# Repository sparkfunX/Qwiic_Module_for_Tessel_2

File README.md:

Qwiic Module for Tessel 2
========================================

[*SPX-14334*](https://www.sparkfun.com/products/14334)

A small breakout board to connect the Tessel 2 to the Qwiic System.

The [Qwiic system](http://www.sparkfun.com/qwiic) enables fast and solderless connection between popular platforms and various sensors and actuators. You can read more about the Qwiic system [here](http://www.sparkfun.com/qwiic). 

License Information
-------------------

This product is _**open source**_!

Please review the LICENSE.md file for license information.

If you have any questions or concerns on licensing, please contact techsupport@sparkfun.com.

Distributed as-is; no warranty is given.

- Your friends at SparkFun.

_<COLLABORATION CREDIT>_

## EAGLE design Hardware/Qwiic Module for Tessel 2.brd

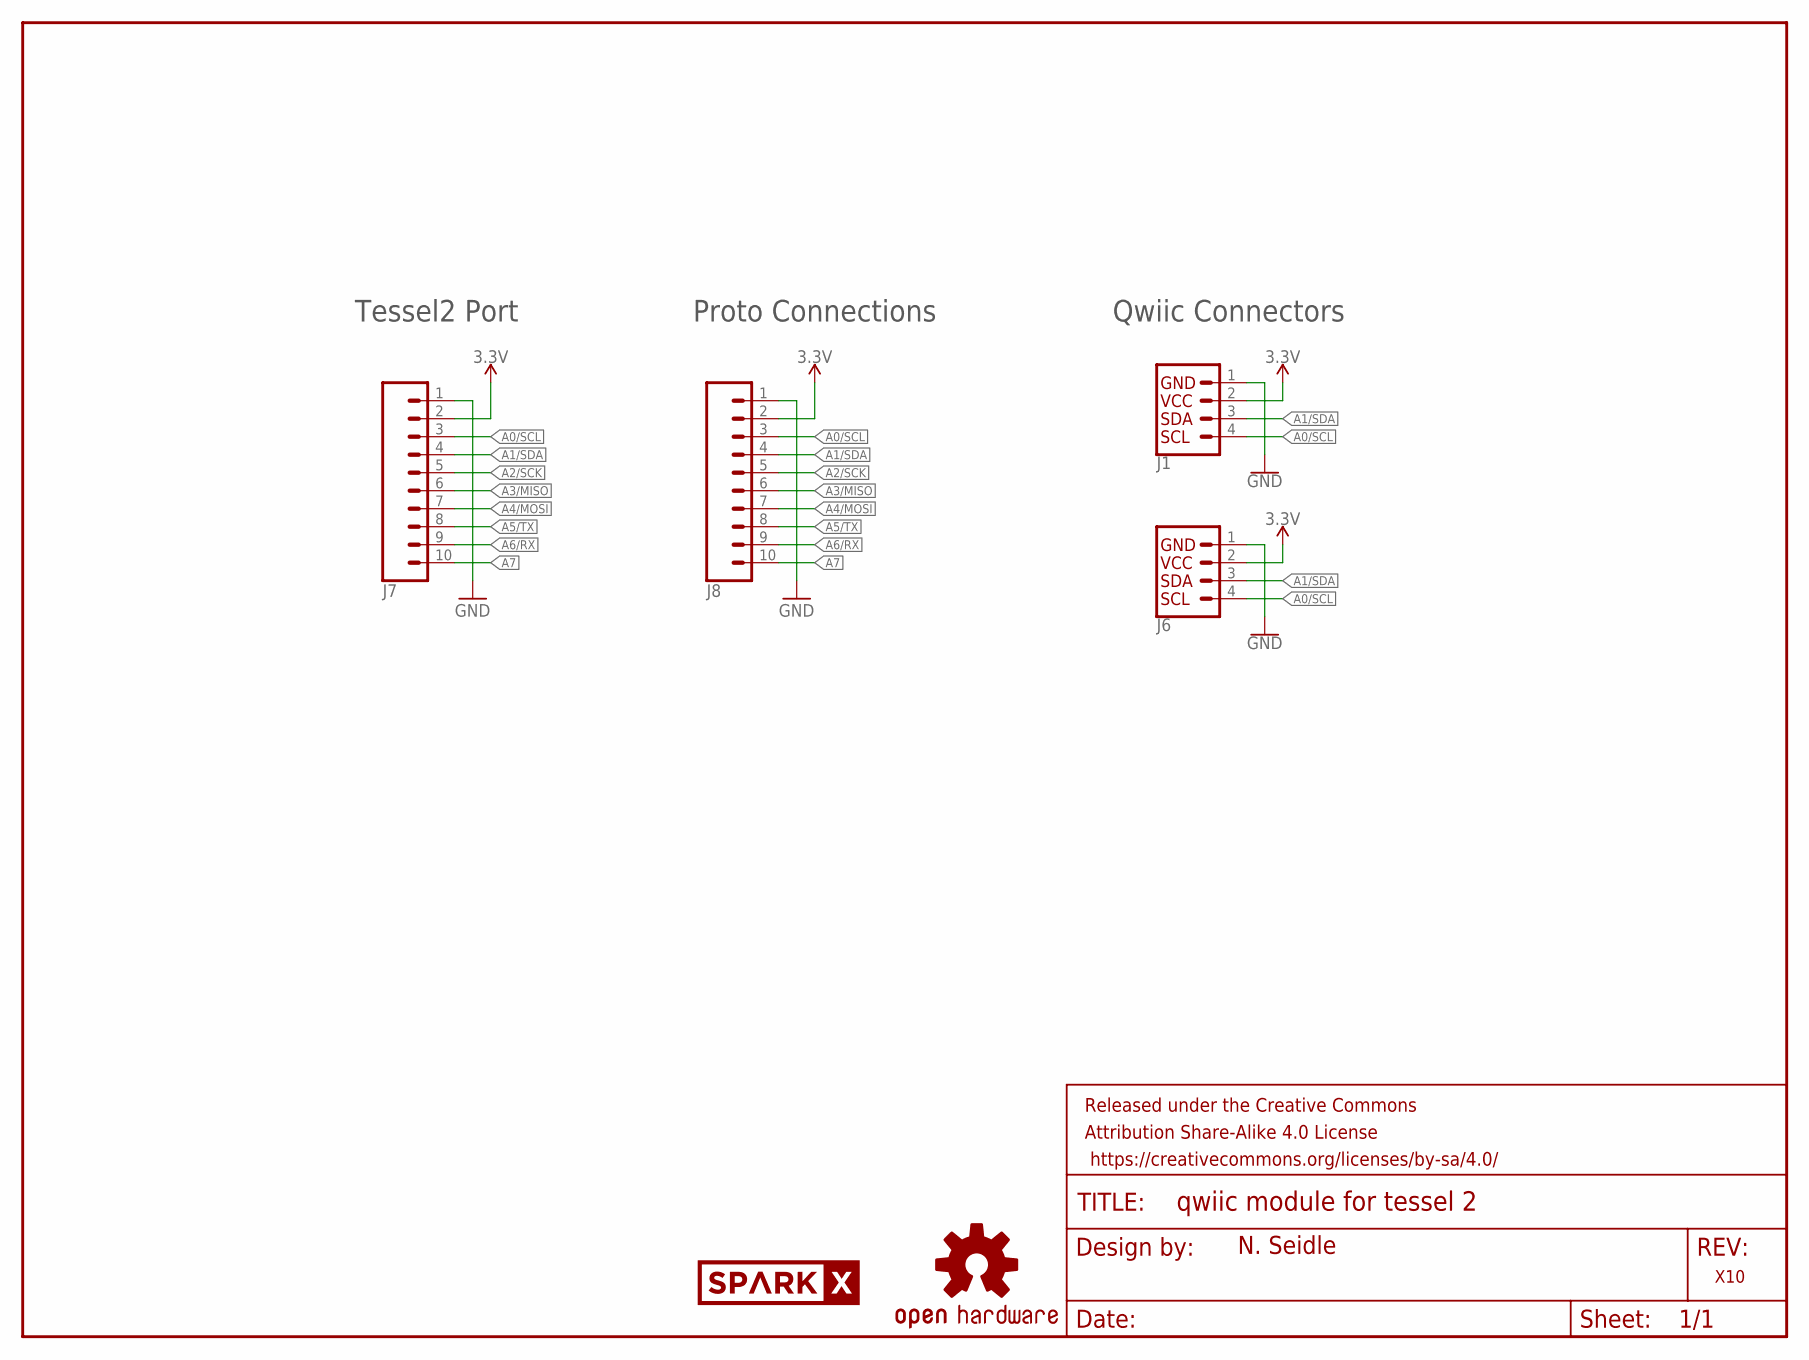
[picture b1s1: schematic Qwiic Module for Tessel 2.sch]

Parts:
FRAME1: FRAME-LETTER; CREATIVE_COMMONS
J1, J6: I2C_STANDARDJS-1MM; 1X04_1MM_RA
J7, J8: CONN_10NO_SILK_PTH_FEMALE; 1X10_NO_SILK
LOGO1: OSHW-LOGOMINI; OSHW-LOGO-MINI
U$2: SPARKX-LOGO4; SPARKX-MEDIUM

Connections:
3.3V: J1.2 (VCC), J6.2 (VCC), J7.2, J8.2
A0/SCL: J1.4 (SCL), J6.4 (SCL), J7.3, J8.3
A1/SDA: J1.3 (SDA), J6.3 (SDA), J7.4, J8.4
A2/SCK: J7.5, J8.5
A3/MISO: J7.6, J8.6
A4/MOSI: J7.7, J8.7
A5/TX: J7.8, J8.8
A6/RX: J7.9, J8.9
A7: J7.10, J8.10
GND: J1.1 (GND), J6.1 (GND), J7.1, J8.1

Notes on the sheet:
N. Seidle
Tessel2 Port
X10
Qwiic Connectors
Proto Connections

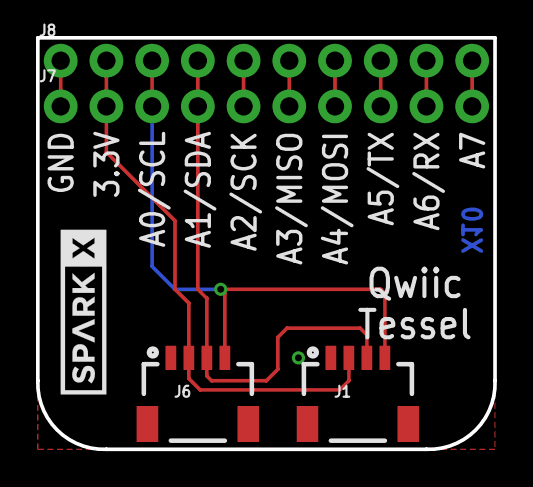
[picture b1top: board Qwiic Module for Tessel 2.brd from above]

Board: 2 copper layers, 25.4 x 22.9 mm, 7 parts (1 on the bottom side), 10 nets.

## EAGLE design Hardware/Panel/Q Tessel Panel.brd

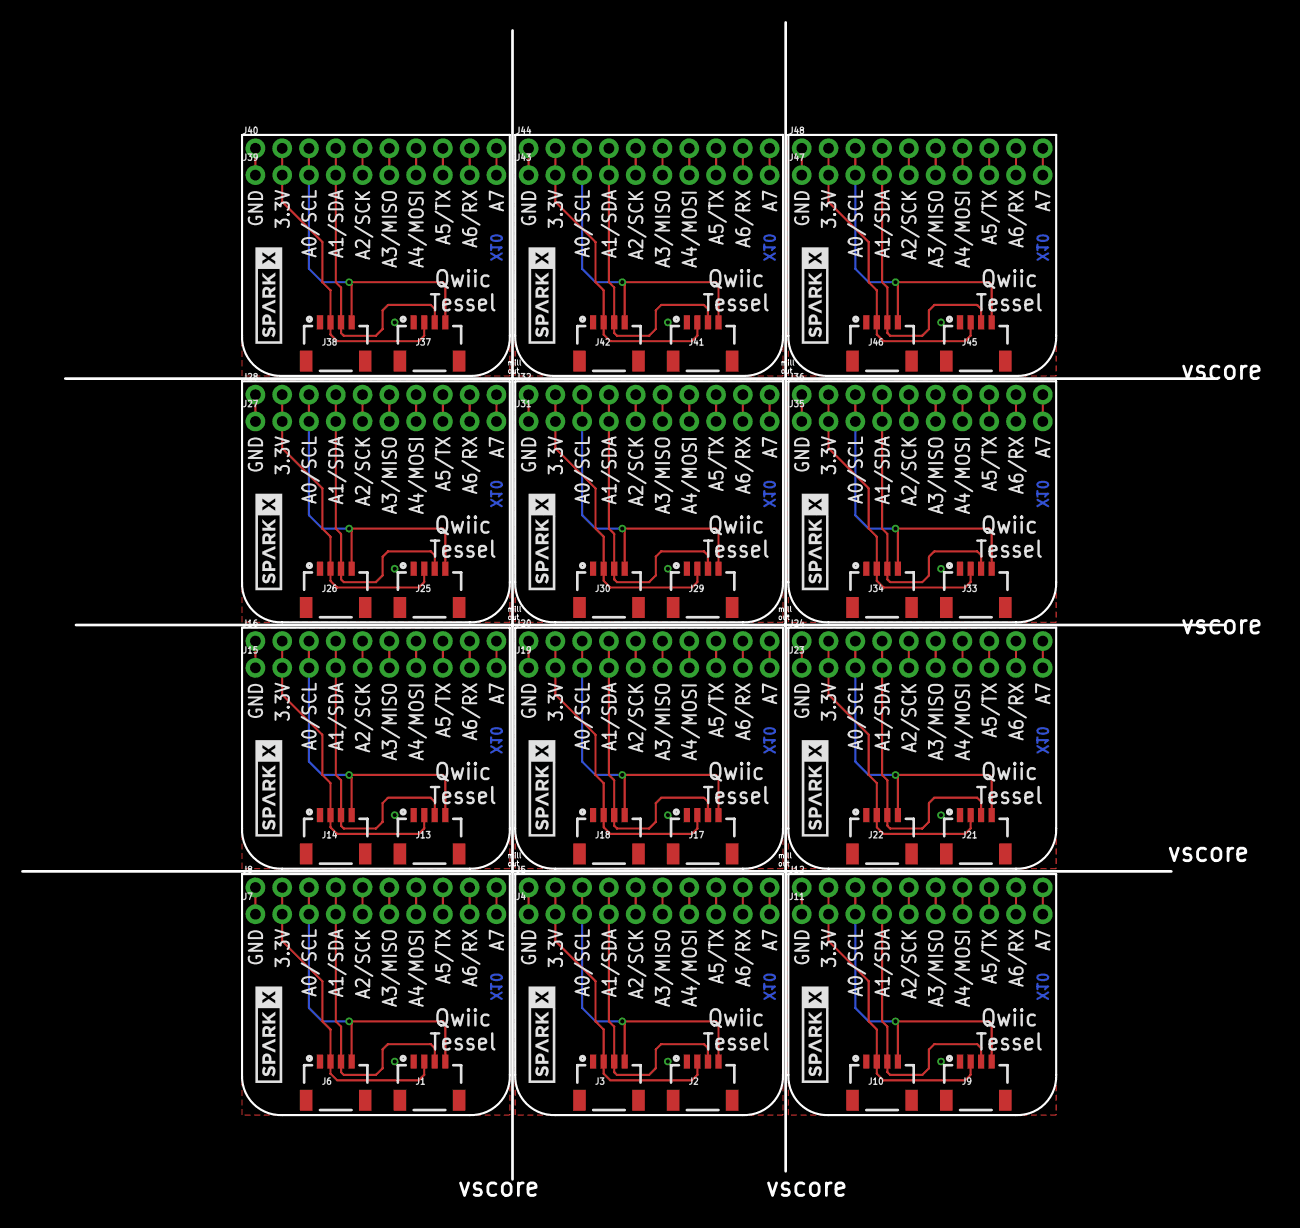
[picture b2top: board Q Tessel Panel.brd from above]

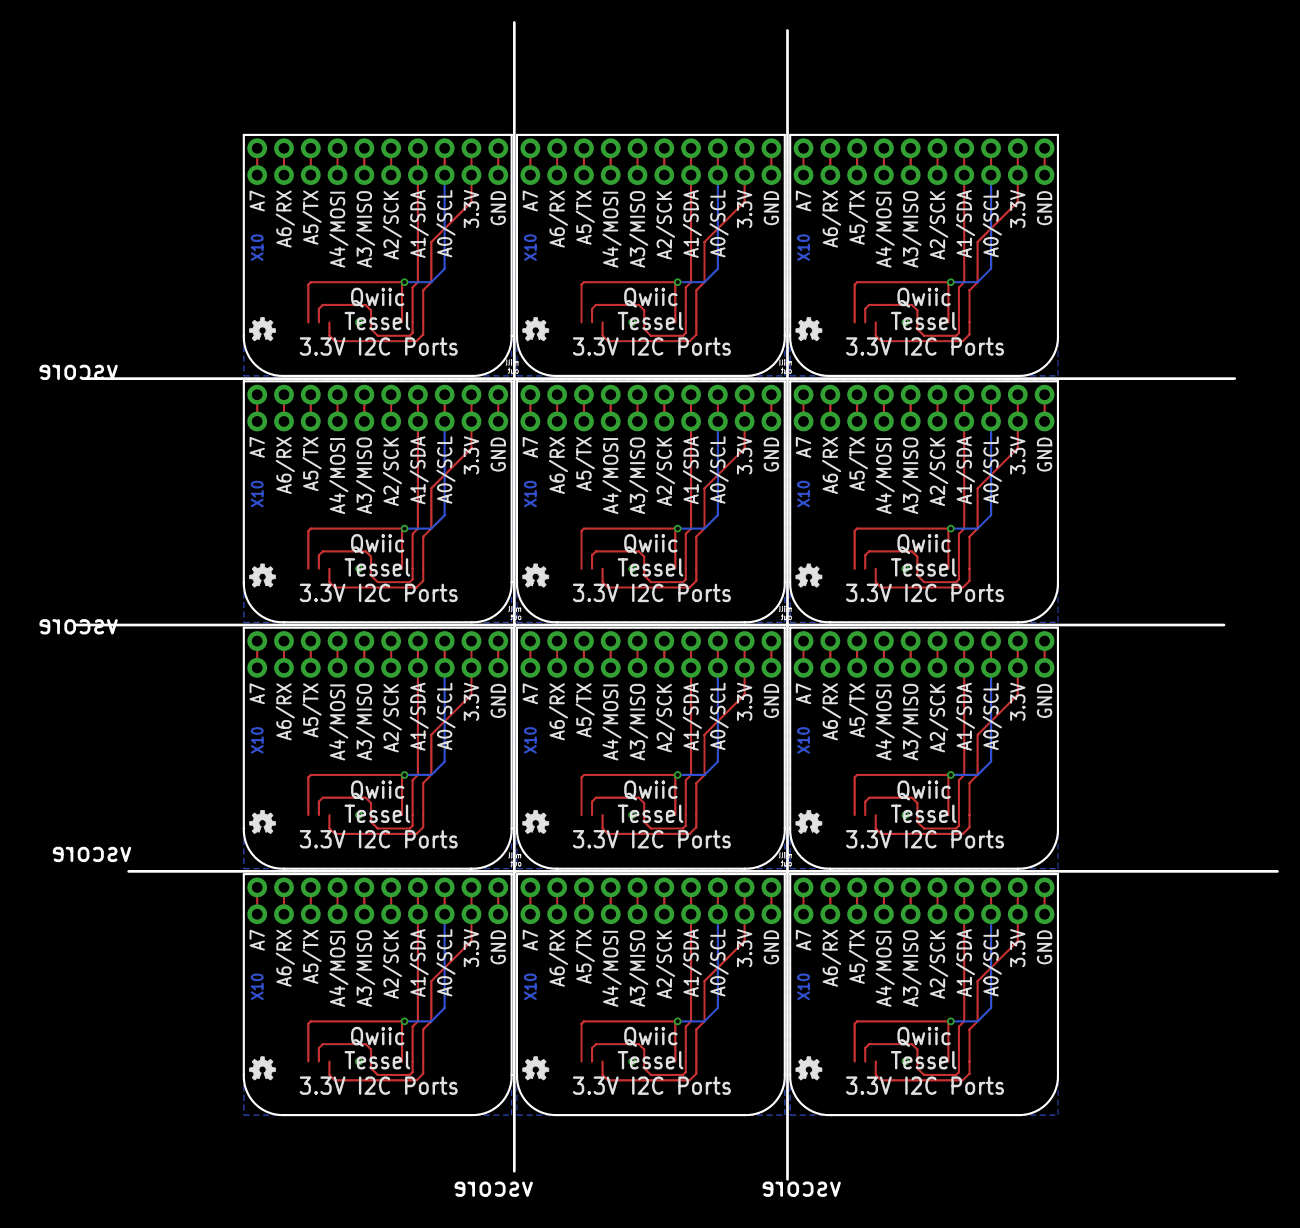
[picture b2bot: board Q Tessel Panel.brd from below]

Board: 2 copper layers, 114.0 x 109.7 mm, 72 parts (12 on the bottom side), 120 nets.

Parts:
J1, J2, J3, J6, J9, J10, J13, J14, J17, J18, J21, J22, J25, J26, J29, J30, J33, J34, J37, J38, J41, J42, J45, J46: 1X04_1MM_RA
J4, J5, J7, J8, J11, J12, J15, J16, J19, J20, J23, J24, J27, J28, J31, J32, J35, J36, J39, J40, J43, J44, J47, J48: 1X10_NO_SILK
LOGO1, LOGO2, LOGO3, LOGO4, LOGO5, LOGO6, LOGO7, LOGO8, LOGO9, LOGO10, LOGO11, LOGO12: OSHW-LOGOMINI; OSHW-LOGO-MINI
U$1, U$2, U$3, U$4, U$5, U$6, U$7, U$8, U$9, U$10, U$11, U$12: SPARKX-LOGO4; SPARKX-MEDIUM

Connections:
3.3V: J1.2, J6.2, J7.2, J8.2
3.3V1: J2.2, J3.2, J4.2, J5.2
3.3V2: J9.2, J10.2, J11.2, J12.2
3.3V3: J13.2, J14.2, J15.2, J16.2
3.3V4: J17.2, J18.2, J19.2, J20.2
3.3V5: J21.2, J22.2, J23.2, J24.2
3.3V6: J25.2, J26.2, J27.2, J28.2
3.3V7: J29.2, J30.2, J31.2, J32.2
3.3V8: J33.2, J34.2, J35.2, J36.2
3.3V9: J37.2, J38.2, J39.2, J40.2
3.3V10: J41.2, J42.2, J43.2, J44.2
3.3V11: J45.2, J46.2, J47.2, J48.2
A0/SCL: J1.4, J6.4, J7.3, J8.3
A0/SCL1: J2.4, J3.4, J4.3, J5.3
A0/SCL2: J9.4, J10.4, J11.3, J12.3
A0/SCL3: J13.4, J14.4, J15.3, J16.3
A0/SCL4: J17.4, J18.4, J19.3, J20.3
A0/SCL5: J21.4, J22.4, J23.3, J24.3
A0/SCL6: J25.4, J26.4, J27.3, J28.3
A0/SCL7: J29.4, J30.4, J31.3, J32.3
A0/SCL8: J33.4, J34.4, J35.3, J36.3
A0/SCL9: J37.4, J38.4, J39.3, J40.3
A0/SCL10: J41.4, J42.4, J43.3, J44.3
A0/SCL11: J45.4, J46.4, J47.3, J48.3
A1: J4.10, J5.10
A1/SDA: J1.3, J6.3, J7.4, J8.4
A1/SDA1: J2.3, J3.3, J4.4, J5.4
A1/SDA2: J9.3, J10.3, J11.4, J12.4
A1/SDA3: J13.3, J14.3, J15.4, J16.4
A1/SDA4: J17.3, J18.3, J19.4, J20.4
A1/SDA5: J21.3, J22.3, J23.4, J24.4
A1/SDA6: J25.3, J26.3, J27.4, J28.4
A1/SDA7: J29.3, J30.3, J31.4, J32.4
A1/SDA8: J33.3, J34.3, J35.4, J36.4
A1/SDA9: J37.3, J38.3, J39.4, J40.4
A1/SDA10: J41.3, J42.3, J43.4, J44.4
A1/SDA11: J45.3, J46.3, J47.4, J48.4
A2: J11.10, J12.10
A2/SCK: J7.5, J8.5
A2/SCK1: J4.5, J5.5
A2/SCK2: J11.5, J12.5
A2/SCK3: J15.5, J16.5
A2/SCK4: J19.5, J20.5
A2/SCK5: J23.5, J24.5
A2/SCK6: J27.5, J28.5
A2/SCK7: J31.5, J32.5
A2/SCK8: J35.5, J36.5
A2/SCK9: J39.5, J40.5
A2/SCK10: J43.5, J44.5
A2/SCK11: J47.5, J48.5
A3: J15.10, J16.10
A3/MISO: J7.6, J8.6
A3/MISO1: J4.6, J5.6
A3/MISO2: J11.6, J12.6
A3/MISO3: J15.6, J16.6
A3/MISO4: J19.6, J20.6
A3/MISO5: J23.6, J24.6
A3/MISO6: J27.6, J28.6
A3/MISO7: J31.6, J32.6
A3/MISO8: J35.6, J36.6
A3/MISO9: J39.6, J40.6
A3/MISO10: J43.6, J44.6
A3/MISO11: J47.6, J48.6
A4: J19.10, J20.10
A4/MOSI: J7.7, J8.7
A4/MOSI1: J4.7, J5.7
A4/MOSI2: J11.7, J12.7
A4/MOSI3: J15.7, J16.7
A4/MOSI4: J19.7, J20.7
A4/MOSI5: J23.7, J24.7
A4/MOSI6: J27.7, J28.7
A4/MOSI7: J31.7, J32.7
A4/MOSI8: J35.7, J36.7
A4/MOSI9: J39.7, J40.7
A4/MOSI10: J43.7, J44.7
A4/MOSI11: J47.7, J48.7
A5: J23.10, J24.10
A5/TX: J7.8, J8.8
A5/TX1: J4.8, J5.8
A5/TX2: J11.8, J12.8
A5/TX3: J15.8, J16.8
A5/TX4: J19.8, J20.8
A5/TX5: J23.8, J24.8
A5/TX6: J27.8, J28.8
A5/TX7: J31.8, J32.8
A5/TX8: J35.8, J36.8
A5/TX9: J39.8, J40.8
A5/TX10: J43.8, J44.8
A5/TX11: J47.8, J48.8
A6: J27.10, J28.10
A6/RX: J7.9, J8.9
A6/RX1: J4.9, J5.9
A6/RX2: J11.9, J12.9
A6/RX3: J15.9, J16.9
A6/RX4: J19.9, J20.9
A6/RX5: J23.9, J24.9
A6/RX6: J27.9, J28.9
A6/RX7: J31.9, J32.9
A6/RX8: J35.9, J36.9
A6/RX9: J39.9, J40.9
A6/RX10: J43.9, J44.9
A6/RX11: J47.9, J48.9
A7: J7.10, J8.10
A8: J31.10, J32.10
A9: J35.10, J36.10
A10: J39.10, J40.10
A11: J43.10, J44.10
A12: J47.10, J48.10
GND: J1.1, J6.1, J7.1, J8.1
GND1: J2.1, J3.1, J4.1, J5.1
GND2: J9.1, J10.1, J11.1, J12.1
GND3: J13.1, J14.1, J15.1, J16.1
GND4: J17.1, J18.1, J19.1, J20.1
GND5: J21.1, J22.1, J23.1, J24.1
GND6: J25.1, J26.1, J27.1, J28.1
GND7: J29.1, J30.1, J31.1, J32.1
GND8: J33.1, J34.1, J35.1, J36.1
GND9: J37.1, J38.1, J39.1, J40.1
GND10: J41.1, J42.1, J43.1, J44.1
GND11: J45.1, J46.1, J47.1, J48.1

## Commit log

2017-06-09 :neckbeard: Added .gitattributes & .gitignore files
2017-12-21 Adding readme

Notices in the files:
parts and their libraries:
SparkFun-Aesthetics: Licensing: CC v3.0 Share-Alike You are welcome to use this library for commercial purposes.
SparkFun-Connectors: Licensing: Creative Commons ShareAlike 4.0 International - https://creativecommons.org/licenses/by-sa/4.0
SparkFun-Aesthetics: Released under the Creative Commons
